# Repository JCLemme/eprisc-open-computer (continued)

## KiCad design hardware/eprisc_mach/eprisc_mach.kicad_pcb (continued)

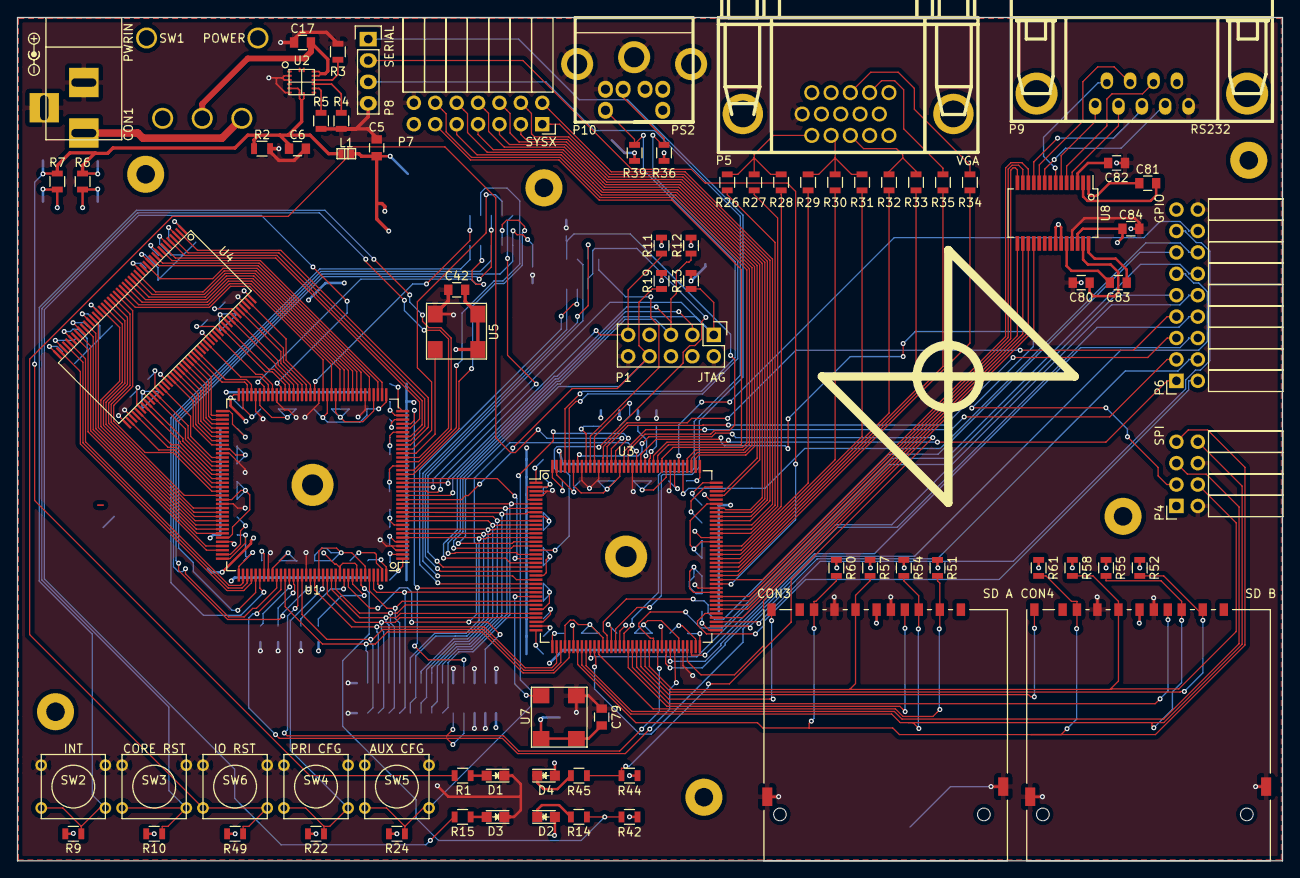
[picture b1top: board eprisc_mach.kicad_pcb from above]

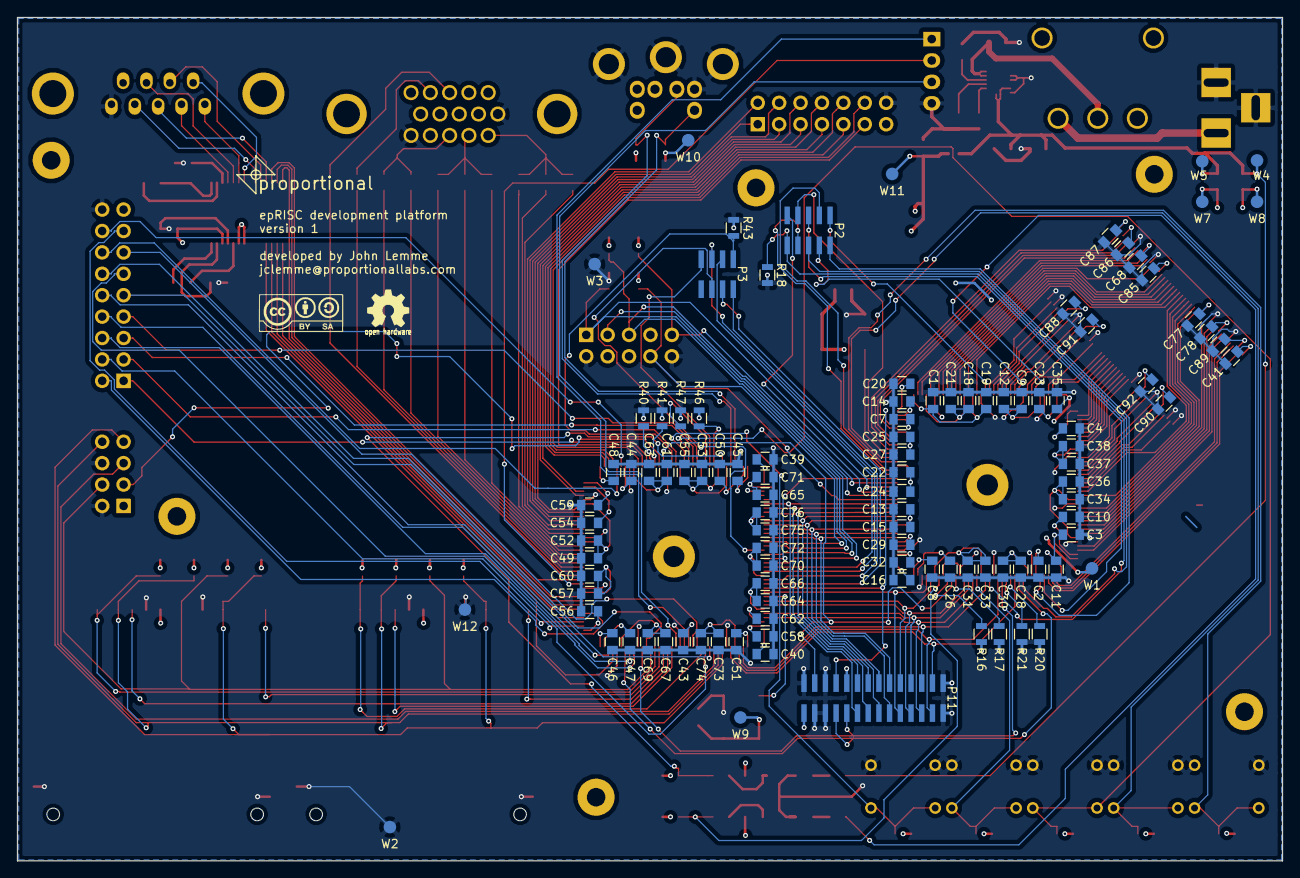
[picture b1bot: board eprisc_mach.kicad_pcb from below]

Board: 4 copper layers, 150.1 x 100.1 mm, 190 parts (107 on the bottom side), 210 nets.

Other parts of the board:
LOGO: logogood
LOGO_TINY: logotiny

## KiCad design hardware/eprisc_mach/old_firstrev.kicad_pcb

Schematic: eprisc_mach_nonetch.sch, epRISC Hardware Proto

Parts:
C1, C2, C3, C4, C7, C8, C9, C10, C11, C13, C14, C16, C18, C19, C20, C22, C23, C25, C26, C28, C29, C31, C32, C34, C35, C37, C40, C42, C43, C44, C45, C46, C47, C48, C49, C50, C51, C53, C54, C56, C57, C58, C59, C61, C62, C64, C65, C67, C68, C70, C71, C73, C75, C78, C79, C80, C81, C82, C83, C84: 0.1u; C_0805
C5: 10u; C_0805
C6: 47u/16v; C_0805
C12, C15, C21, C24, C27, C30, C33, C36, C38, C39, C41, C52, C55, C60, C63, C66, C69, C72, C74, C76, C77: 1u; C_0805
C17: 4.7u; C_0805
CON1: POWER_IN_5V; BARREL_JACK
CON2: SD_INT; microsd_socket
CON3: SD_A; SD_Card_Receptacle
CON4: SD_B; SD_Card_Receptacle
D1: GREEN; LED_0805
D2, D4: CONF_DONE; LED_0805
D3: HALT; LED_0805
L1: 600o/500mA; inductor_smd_4.8x2.8mm
L2, L3: FERRITE_BEAD; inductor_smd_0805
P1: PRI_PROG; Pin_Header_Straight_2x05
P2: PRI_DBG; Pin_Header_Straight_2x05
P3: AUX_DBG; Pin_Header_Straight_2x04
P4: AUX_PROG; Pin_Header_Straight_2x05
P5: VGA; DB_15F-VGA
P6: GPIO; Socket_Strip_Angled_2x09
P7: SYSX_EXT; Socket_Strip_Angled_2x07
P8: TTL_SERIAL; Socket_Strip_Straight_1x04
P9: RS232; DB_9F
P10: PS2; minidin-8
P11: SYSX_INT; bb080_28
R1, R13, R14, R15, R16, R17, R27, R30, R32, R38, R45, R46, R47: 1K; R_0805
R2: DNI; R_0805
R3, R4, R5, R8, R20, R21, R23, R40, R41: 0; R_0805
R6, R7: 0.1; R_0805
R9, R10, R42, R44: 3.3K; R_0805
R11, R12, R18, R19, R22, R24, R25, R36, R37, R39, R43, R48, R49: 10K; R_0805
R26, R29: 2K; R_0805
R28, R31, R33: 510; R_0805
R34, R35: 100; R_0805
R50, R51, R52, R53, R54, R55, R56, R57, R58, R59, R60, R61: 50K; R_0805
SW1: POWER; SW_SPDT
SW2: CORE_INT; smd_push2
SW3: CORE_RST; smd_push2
SW4: PRI_CONFIG; smd_push2
SW5: AUX_CONFIG; smd_push2
SW6: IO_RST; smd_push2
U1, U6: MAX10-10M16SA-E144; LQFP-144_20x20mm_Pitch0.5mm
U2: EP5388QI; QFN-16-ALTERA
U3: MCP1525; SOT-23
U4: IS45S32800J; TSOP-86
U5, U7: CB3LV-3C-50M0000; CRYSTAL_CTS
U8: MAX3244; SSOP-28_5.3x10.2mm_Pitch0.65mm
W1, W4, W5, W7, W8: TEST_1P; Measurement_Point_Round-SMD-Pad_Small
W2, W3, W6, W12: GND; Measurement_Point_Round-SMD-Pad_Small
W9: V_CORE; Measurement_Point_Round-SMD-Pad_Small
W10: V_IO; Measurement_Point_Round-SMD-Pad_Small
W11: V_VCCIO; Measurement_Point_Round-SMD-Pad_Small
W13: GNDA; Measurement_Point_Round-SMD-Pad_Small
W14: V_REF; Measurement_Point_Round-SMD-Pad_Small

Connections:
+2V5: C39.1, C41.1, C77.1, U1.5, U3.2, U6.5, W14.1
+3V3: C6.1, L1.1, R1.2, R2.1, R6.1, R7.1, U2.5 (VSENSE), U2.7 (VOUT), U2.8 (VOUT), W4.1, W5.1
+5V: C17.1, P10.4, SW1.2, U2.13 (ENABLE), U2.14 (VIN)
/AUX_CLK: U6.28, U7.3 (OUT)
/AUX_CONFDONE: R44.2, R45.2, U6.138
/AUX_CONFSEL: P3.1, R43.2, U6.126
/AUX_CRCERR: R47.2, U6.134
/AUX_DBG0: P3.3, U6.21
/AUX_DBG1: P3.5, U6.22
/AUX_DBG2: P3.2, U6.24
/AUX_DBG3: P3.4, U6.25
/AUX_DBG4: P3.6, U6.17
/AUX_DBG5: P3.7, U6.135
/AUX_DBG6: P3.8, U6.123
/AUX_DEVCLRN: R40.1, U6.121
/AUX_DEVOE: R41.1, U6.122
/AUX_JTAGEN: P4.8, R48.1, U6.15
/AUX_NCONFIG: R24.1, SW5.2, U6.129
/AUX_NSTATUS: R46.2, U6.136
/AUX_RST: R49.1, SW6.2, U6.130
/AUX_TCK: P4.1, R38.2, U6.18
/AUX_TDI: P4.9, R25.1, U6.19
/AUX_TDO: P4.3, U6.20
/AUX_TMS: P4.5, R37.1, U6.16
/BUS_CLK: P11.21, U1.33, U6.26
/BUS_INT: P11.25, U1.135, U6.124
/BUS_MISO0: P11.3, U1.141, U6.65
/BUS_MISO1: P11.15, U1.140, U6.69
/BUS_MISO2: P11.11, U1.130, U6.27
/BUS_MISO3: P11.13, U1.131, U6.29
/BUS_MISO4: P11.9, U1.132, U6.32
/BUS_MISO5: P11.7, U1.127, U6.33
/BUS_MISO6: P11.5, U1.124, U6.30
/BUS_MISO7: P11.17, U1.120, U6.64
/BUS_MOSI0: P11.4, U1.6, U6.6
/BUS_MOSI1: P11.6, U1.7, U6.7
/BUS_MOSI2: P11.8, U1.8, U6.8
/BUS_MOSI3: P11.10, U1.10, U6.10
/BUS_MOSI4: P11.12, U1.11, U6.11
/BUS_MOSI5: P11.14, U1.12, U6.12
/BUS_MOSI6: P11.16, U1.13, U6.13
/BUS_MOSI7: P11.18, U1.14, U6.14
/BUS_SS0: P11.20, U1.123, U6.62
/BUS_SS1: P11.22, U1.111, U6.66
/EXB_CLK: P7.12, U6.84
/EXB_INT: P7.11, U6.80
/EXB_MISO0: P7.1, U6.75
/EXB_MISO1: P7.3, U6.77
/EXB_MISO2: P7.5, U6.74
/EXB_MISO3: P7.7, U6.76
/EXB_MOSI0: P7.2, U6.79
/EXB_MOSI1: P7.4, U6.81
/EXB_MOSI2: P7.6, U6.85
/EXB_MOSI3: P7.8, U6.87
/EXB_SS0: P7.9, U6.86
/EXB_SS1: P7.10, U6.78
/GIO_PIN0: P6.1, U6.99
/GIO_PIN1: P6.3, U6.101
/GIO_PIN2: P6.5, U6.100
/GIO_PIN3: P6.7, U6.102
/GIO_PIN4: P6.9, U6.105
/GIO_PIN5: P6.11, U6.106
/GIO_PIN6: P6.13, U6.97
/GIO_PIN7: P6.15, U6.110
/GIO_PIN8: P6.2, U6.111
/GIO_PIN9: P6.4, U6.118
/GIO_PIN10: P6.6, U6.119
/GIO_PIN11: P6.8, U6.112
/GIO_PIN12: P6.10, U6.70
/GIO_PIN13: P6.12, U6.61
/GIO_PIN14: P6.14, U6.113
/GIO_PIN15: P6.16, U6.114
/MEM_A0: U1.61, U4.25 (A0)
/MEM_A1: U1.65, U4.26 (A1)
/MEM_A2: U1.64, U4.27 (A2)
/MEM_A3: U1.96, U4.60 (A3)
/MEM_A4: U1.93, U4.61 (A4)
/MEM_A5: U1.92, U4.62 (A5)
/MEM_A6: U1.91, U4.63 (A6)
/MEM_A7: U1.90, U4.64 (A7)
/MEM_A8: U1.89, U4.65 (A8)
/MEM_A9: U1.88, U4.66 (A9)
/MEM_A10: U1.44, U4.24 (A10)
/MEM_A11: U1.45, U4.21 (A11)
/MEM_BA0: U1.43, U4.22 (BA0)
/MEM_BA1: U1.41, U4.23 (BA1)
/MEM_CASn: U1.119, U4.18 (CASn)
/MEM_CKE: U1.110, U4.67 (CKE)
/MEM_CLK: U1.32, U4.68 (CLK)
/MEM_CSn: U1.114, U4.20 (CSn)
/MEM_DQ0: U1.55, U4.2 (DQ0)
/MEM_DQ1: U1.56, U4.4 (DQ1)
/MEM_DQ2: U1.57, U4.5 (DQ2)
/MEM_DQ3: U1.58, U4.7 (DQ3)
/MEM_DQ4: U1.46, U4.8 (DQ4)
/MEM_DQ5: U1.47, U4.10 (DQ5)
/MEM_DQ6: U1.50, U4.11 (DQ6)
/MEM_DQ7: U1.52, U4.13 (DQ7)
/MEM_DQ8: U1.60, U4.74 (DQ8)
/MEM_DQ9: U1.87, U4.76 (DQ9)
/MEM_DQ10: U1.86, U4.77 (DQ10)
/MEM_DQ11: U1.48, U4.79 (DQ11)
/MEM_DQ12: U1.85, U4.80 (DQ12)
/MEM_DQ13: U1.84, U4.82 (DQ13)
/MEM_DQ14: U1.81, U4.83 (DQ14)
/MEM_DQ15: U1.80, U4.85 (DQ15)
/MEM_DQ16: U1.69, U4.31 (DQ16)
/MEM_DQ17: U1.70, U4.33 (DQ17)
/MEM_DQ18: U1.74, U4.34 (DQ18)
/MEM_DQ19: U1.75, U4.36 (DQ19)
/MEM_DQ20: U1.76, U4.37 (DQ20)
/MEM_DQ21: U1.77, U4.39 (DQ21)
/MEM_DQ22: U1.78, U4.40 (DQ22)
/MEM_DQ23: U1.79, U4.42 (DQ23)
/MEM_DQ24: U1.106, U4.45 (DQ24)
/MEM_DQ25: U1.105, U4.47 (DQ25)
/MEM_DQ26: U1.102, U4.48 (DQ26)
/MEM_DQ27: U1.101, U4.50 (DQ27)
/MEM_DQ28: U1.100, U4.51 (DQ28)
/MEM_DQ29: U1.99, U4.53 (DQ29)
/MEM_DQ30: U1.98, U4.54 (DQ30)
/MEM_DQ31: U1.97, U4.56 (DQ31)
/MEM_DQM0: U1.21, U4.16 (DQM0)
/MEM_DQM1: U1.22, U4.71 (DQM1)
/MEM_DQM2: U1.24, U4.28 (DQM2)
/MEM_DQM3: U1.25, U4.59 (DQM3)
/MEM_RASn: U1.112, U4.19 (RASn)
/MEM_WEn: U1.118, U4.17 (WEn)
/PRI_CLK: U1.26, U5.3 (OUT)
/PRI_CONFDONE: R14.2, R42.2, U1.138
/PRI_CONFSEL: P2.1, R18.2, U1.126
/PRI_CRCERR: R17.2, U1.134
/PRI_DBG0: P2.2, U1.17
/PRI_DBG1: P2.4, U1.27
/PRI_DBG2: P2.6, U1.39
/PRI_DBG3: P2.8, U1.59
/PRI_DBG4: P2.10, U1.54
/PRI_DBG5: P2.9, U1.113
/PRI_DBGRX: P2.5, U1.38
/PRI_DBGTX: P2.7, U1.66
/PRI_DEVCLRN: R20.1, U1.121
/PRI_DEVOE: R21.1, U1.122
/PRI_FDBG: P2.3, U1.30
/PRI_FHLT: R15.2, U1.62
/PRI_INT: R9.1, SW2.2, U1.28
/PRI_JTAGEN: P1.8, R19.1, U1.15
/PRI_NCONFIG: R22.1, SW4.2, U1.129
/PRI_NSTATUS: R16.2, U1.136
/PRI_RST: R10.1, SW3.2, U1.29
/PRI_TCK: P1.1, R13.2, U1.18
/PRI_TDI: P1.9, R11.1, U1.19
/PRI_TDO: P1.3, U1.20
/PRI_TMS: P1.5, R12.1, U1.16
/PS2_CLK: P10.5, R39.2, U6.141
/PS2_DAT: P10.1, R36.2, U6.140
/SER_CTS: U6.45, U8.16 (R_OUT)
/SER_DCD: U6.48, U8.17 (R_OUT)
/SER_DSR: U6.43, U8.18 (R_OUT)
/SER_DTR: U6.41, U8.12 (T_IN)
/SER_RTS: U6.44, U8.13 (T_IN)
/SER_RX: U6.59, U8.15 (R_OUT)
/SER_TX: U6.60, U8.14 (T_IN)
/SPI_CD0: CON3.10 (CARD_DETECT), U6.131
/SPI_CD1: CON4.10 (CARD_DETECT), U6.132
/SPI_MISO: CON2.7, CON3.7 (DAT0), CON4.7 (DAT0), R59.2, R60.2, R61.2, U6.90
/SPI_MOSI: CON2.3, CON3.2 (CMD), CON4.2 (CMD), R53.2, R54.2, R55.2, U6.91
/SPI_SCLK: CON2.5, CON3.5 (CLK), CON4.5 (CLK), R56.2, R57.2, R58.2, U6.98
/SPI_SS0: CON2.2, R50.2, U6.92
/SPI_SS1: CON3.1 (CD/DAT3), R51.2, U6.93
/SPI_SS2: CON4.1 (CD/DAT3), R52.2, U6.96
/SPI_WP0: CON3.11 (WRITE_PROTECT), U6.120
/SPI_WP1: CON4.11 (WRITE_PROTECT), U6.127
/TTL_RTS: P8.3, U6.54
/TTL_RX: P8.1, U6.88
/TTL_TX: P8.2, U6.89
/VGA_B0: R32.2, U6.50
/VGA_B1: R33.2, U6.52
/VGA_G0: R29.2, U6.58
/VGA_G1: R30.2, U6.46
/VGA_G2: R31.2, U6.47
/VGA_HS: R34.2, U6.38
/VGA_R0: R26.2, U6.55
/VGA_R1: R27.2, U6.56
/VGA_R2: R28.2, U6.57
/VGA_VS: R35.2, U6.39
unnamed: C40.1, R8.1, U1.3
unnamed: C78.1, R23.1, U6.3
unnamed: C80.1, U8.27 (V+)
unnamed: C81.1, U8.1 (C2+)
unnamed: C81.2, U8.2 (C2-)
unnamed: C82.2, U8.3 (V-)
unnamed: C83.1, U8.28 (C1+)
unnamed: C83.2, U8.24 (C1-)
unnamed: CON1.1, SW1.1
unnamed: D1.2 (A), R1.1
unnamed: D2.2 (A), R14.1
unnamed: D3.2 (A), R15.1
unnamed: D4.2 (A), R45.1
unnamed: L2.1, U1.4
unnamed: L3.1, U6.4
unnamed: P5.1, R26.1, R27.1, R28.1
unnamed: P5.2, R29.1, R30.1, R31.1
unnamed: P5.3, R32.1, R33.1
unnamed: P5.13, R34.1
unnamed: P5.14, R35.1
unnamed: P9.1, U8.6 (R_IN)
unnamed: P9.2, U8.4 (R_IN)
unnamed: P9.3, U8.11 (T_OUT)
unnamed: P9.4, U8.9 (T_OUT)
unnamed: P9.6, U8.7 (R_IN)
unnamed: P9.7, U8.10 (T_OUT)
unnamed: P9.8, U8.5 (R_IN)
unnamed: R3.1, U2.12 (VS2)
unnamed: R4.1, U2.11 (VS1)
unnamed: R5.1, U2.10 (VS0)
VAA: C9.1, C12.1, C13.1, C15.1, C18.1, C21.1, C22.1, C24.1, C25.1, C27.1, C28.1, C30.1, C31.1, C33.1, C34.1, C36.1, C37.1, C38.1, C49.1, C52.1, C53.1, C55.1, C57.1, C60.1, C61.1, C63.1, C64.1, C66.1, C67.1, C69.1, C70.1, C72.1, C73.1, C74.1, C75.1, C76.1, C84.1, CON2.4, CON3.4 (VDD), CON4.4 (VDD), P1.4, P4.4, P6.17, P7.13, P11.28, R7.2, R9.2, R10.2, R11.2, R12.2, R16.1, R17.1, R19.2, R22.2, R24.2, R25.2, R36.1, R37.2, R39.1, R42.1, R44.1, R46.1, R47.1, R48.2, R49.2, R50.1, R51.1, R52.1, R53.1, R54.1, R55.1, R56.1, R57.1, R58.1, R59.1, R60.1, R61.1, U1.9, U1.23, U1.31, U1.40, U1.49, U1.67, U1.82, U1.94, U1.103, U1.117, U1.128, U1.139, U4.3 (VDDq), U4.9 (VDDq), U4.35 (VDDq), U4.41 (VDDq), U4.49 (VDDq), U4.55 (VDDq), U4.75 (VDDq), U4.81 (VDDq), U6.9, U6.23, U6.31, U6.40, U6.49, U6.67, U6.82, U6.94, U6.103, U6.117, U6.128, U6.139, U8.22 (FORCEOFFn), U8.23 (FORCEON), U8.26 (VCC), W8.1, W10.1
VCC: C1.1, C2.1, C3.1, C4.1, C7.1, C10.1, C14.1, C19.1, C23.1, C26.1, C29.1, C32.1, C42.2, C43.1, C44.1, C45.1, C46.1, C47.1, C50.1, C54.1, C58.1, C62.1, C65.1, C68.1, C71.1, C79.2, R6.2, U1.2, U1.34, U1.35, U1.71, U1.107, U1.143, U4.1 (VDD), U4.15 (VDD), U4.29 (VDD), U4.43 (VDD), U5.1 (EN), U5.4 (VCC), U6.2, U6.34, U6.35, U6.71, U6.107, U6.143, U7.1 (EN), U7.4 (VCC), W7.1, W9.1
VEE: C5.1, C8.1, C11.1, C16.1, C20.1, C35.1, C48.1, C51.1, C56.1, C59.1, L1.2, U1.1, U1.36, U1.37, U1.51, U1.72, U1.73, U1.108, U1.109, U1.115, U1.144, U3.1, U6.1, U6.36, U6.37, U6.51, U6.72, U6.73, U6.108, U6.109, U6.115, U6.144, W1.1, W11.1

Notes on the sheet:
What're these for?

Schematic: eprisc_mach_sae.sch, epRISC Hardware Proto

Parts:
C1, C2, C3, C4, C7, C8, C9, C10, C11, C13, C14, C16, C18, C19, C20, C22, C23, C25, C26, C28, C29, C31, C32, C34, C35, C37, C40, C42, C43, C44, C45, C46, C47, C48, C49, C50, C51, C53, C54, C56, C57, C58, C59, C61, C62, C64, C65, C67, C68, C70, C71, C73, C75, C78, C79, C80, C81, C82, C83, C84: 0.1u; C_0805
C5: 10u; C_0805
C6: 47u/16v; C_0805
C12, C15, C21, C24, C27, C30, C33, C36, C38, C39, C41, C52, C55, C60, C63, C66, C69, C72, C74, C76, C77: 1u; C_0805
C17: 4.7u; C_0805
CON1: POWER_IN_5V; BARREL_JACK
CON2: SD_INT; microsd_socket
CON3: SD_A; SD_Card_Receptacle
CON4: SD_B; SD_Card_Receptacle
D1: GREEN; LED_0805
D2, D4: CONF_DONE; LED_0805
D3: HALT; LED_0805
L1: 600o/500mA; inductor_smd_0603
L2, L3: FERRITE_BEAD; inductor_smd_0402
P1: PRI_PROG; SMD_STRIP_10
P2: PRI_DBG; SMD_STRIP_10
P3: AUX_DBG; SMD_STRIP_8
P4: AUX_PROG; SMD_STRIP_10
P5: VGA; DB15F-VGA-AMP
P6: GPIO; Socket_Strip_Angled_2x09
P7: SYSX_EXT; Socket_Strip_Angled_2x07
P8: TTL_SERIAL; Socket_Strip_Straight_1x04
P9: RS232; DB_9F
P10: PS2; 00JG-MiniDin6
P11: SYSX_INT; SMD_STRIP_28
R1, R13, R14, R15, R16, R17, R27, R30, R32, R38, R45, R46, R47: 1K; R_0805
R2: DNI; R_0805
R3, R4, R5, R8, R20, R21, R23, R40, R41: 0; R_0805
R6, R7: 0.1; R_0805
R9, R10, R42, R44: 3.3K; R_0805
R11, R12, R18, R19, R22, R24, R25, R36, R37, R39, R43, R48, R49, R50, R51, R52, R53, R54, R55, R56, R57, R58, R59, R60, R61: 10K; R_0805
R26, R29: 2K; R_0805
R28, R31, R33: 510; R_0805
R34, R35: 100; R_0805
SW1: POWER; SW_SLIDE_PWR
SW2: CORE_INT; smd_push2
SW3: CORE_RST; smd_push2
SW4: PRI_CONFIG; smd_push2
SW5: AUX_CONFIG; smd_push2
SW6: IO_RST; smd_push2
U1, U6: MAX10-10M16SA-E144; LQFP-144_20x20mm_Pitch0.5mm
U2: EP5388QI; QFN-16-ALTERA
U3: MCP1525; SOT-23
U4: IS45S32800J; TSOP-86
U5, U7: CB3LV-3C-50M0000; CRYSTAL_CTS
U8: MAX3244; SSOP-28_5.3x10.2mm_Pitch0.65mm
W1, W4, W5, W7, W8: TEST_1P; Measurement_Point_Round-SMD-Pad_Small
W2, W3, W6, W12: GND; Measurement_Point_Round-SMD-Pad_Small
W9: V_CORE; Measurement_Point_Round-SMD-Pad_Small
W10: V_IO; Measurement_Point_Round-SMD-Pad_Small
W11: V_VCCIO; Measurement_Point_Round-SMD-Pad_Small
W13: GNDA; Measurement_Point_Round-SMD-Pad_Small
W14: V_REF; Measurement_Point_Round-SMD-Pad_Small

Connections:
+2V5: C39.1, C41.1, C77.1, U1.5, U3.2, U6.5, W14.1
+3V3: C6.1, L1.1, R1.2, R2.1, R6.1, R7.1, U2.5 (VSENSE), U2.7 (VOUT), U2.8 (VOUT), W4.1, W5.1
+5V: C17.1, P10.4, SW1.2, U2.13 (ENABLE), U2.14 (VIN)
/AUX_CLK: U6.28, U7.3 (OUT)
/AUX_CONFDONE: R44.2, R45.2, U6.138
/AUX_CONFSEL: P3.1, R43.2, U6.126
/AUX_CRCERR: R47.2, U6.134
/AUX_DBG0: P3.3, U6.21
/AUX_DBG1: P3.5, U6.22
/AUX_DBG2: P3.2, U6.24
/AUX_DBG3: P3.4, U6.25
/AUX_DBG4: P3.6, U6.17
/AUX_DBG5: P3.7, U6.135
/AUX_DBG6: P3.8, U6.123
/AUX_DEVCLRN: R40.1, U6.121
/AUX_DEVOE: R41.1, U6.122
/AUX_JTAGEN: P4.8, R48.1, U6.15
/AUX_NCONFIG: R24.1, SW5.2, U6.129
/AUX_NSTATUS: R46.2, U6.136
/AUX_RST: R49.1, SW6.2, U6.130
/AUX_TCK: P4.1, R38.2, U6.18
/AUX_TDI: P4.9, R25.1, U6.19
/AUX_TDO: P4.3, U6.20
/AUX_TMS: P4.5, R37.1, U6.16
/BUS_CLK: P11.21, U1.33, U6.26
/BUS_INT: P11.25, U1.135, U6.124
/BUS_MISO0: P11.3, U1.141, U6.65
/BUS_MISO1: P11.15, U1.140, U6.69
/BUS_MISO2: P11.11, U1.130, U6.27
/BUS_MISO3: P11.13, U1.131, U6.29
/BUS_MISO4: P11.9, U1.132, U6.32
/BUS_MISO5: P11.7, U1.127, U6.33
/BUS_MISO6: P11.5, U1.124, U6.30
/BUS_MISO7: P11.17, U1.120, U6.64
/BUS_MOSI0: P11.4, U1.6, U6.6
/BUS_MOSI1: P11.6, U1.7, U6.7
/BUS_MOSI2: P11.8, U1.8, U6.8
/BUS_MOSI3: P11.10, U1.10, U6.10
/BUS_MOSI4: P11.12, U1.11, U6.11
/BUS_MOSI5: P11.14, U1.12, U6.12
/BUS_MOSI6: P11.16, U1.13, U6.13
/BUS_MOSI7: P11.18, U1.14, U6.14
/BUS_SS0: P11.20, U1.123, U6.62
/BUS_SS1: P11.22, U1.111, U6.66
/EXB_CLK: P7.12, U6.84
/EXB_INT: P7.11, U6.80
/EXB_MISO0: P7.1, U6.75
/EXB_MISO1: P7.3, U6.77
/EXB_MISO2: P7.5, U6.74
/EXB_MISO3: P7.7, U6.76
/EXB_MOSI0: P7.2, U6.79
/EXB_MOSI1: P7.4, U6.81
/EXB_MOSI2: P7.6, U6.85
/EXB_MOSI3: P7.8, U6.87
/EXB_SS0: P7.9, U6.86
/EXB_SS1: P7.10, U6.78
/GIO_PIN0: P6.1, U6.99
/GIO_PIN1: P6.3, U6.101
/GIO_PIN2: P6.5, U6.100
/GIO_PIN3: P6.7, U6.102
/GIO_PIN4: P6.9, U6.105
/GIO_PIN5: P6.11, U6.106
/GIO_PIN6: P6.13, U6.97
/GIO_PIN7: P6.15, U6.110
/GIO_PIN8: P6.2, U6.111
/GIO_PIN9: P6.4, U6.118
/GIO_PIN10: P6.6, U6.119
/GIO_PIN11: P6.8, U6.112
/GIO_PIN12: P6.10, U6.70
/GIO_PIN13: P6.12, U6.61
/GIO_PIN14: P6.14, U6.113
/GIO_PIN15: P6.16, U6.114
/MEM_A0: U1.61, U4.25 (A0)
/MEM_A1: U1.65, U4.26 (A1)
/MEM_A2: U1.64, U4.27 (A2)
/MEM_A3: U1.96, U4.60 (A3)
/MEM_A4: U1.93, U4.61 (A4)
/MEM_A5: U1.92, U4.62 (A5)
/MEM_A6: U1.91, U4.63 (A6)
/MEM_A7: U1.90, U4.64 (A7)
/MEM_A8: U1.89, U4.65 (A8)
/MEM_A9: U1.88, U4.66 (A9)
/MEM_A10: U1.44, U4.24 (A10)
/MEM_A11: U1.45, U4.21 (A11)
/MEM_BA0: U1.43, U4.22 (BA0)
/MEM_BA1: U1.41, U4.23 (BA1)
/MEM_CASn: U1.119, U4.18 (CASn)
/MEM_CKE: U1.110, U4.67 (CKE)
/MEM_CLK: U1.32, U4.68 (CLK)
/MEM_CSn: U1.114, U4.20 (CSn)
/MEM_DQ0: U1.55, U4.2 (DQ0)
/MEM_DQ1: U1.56, U4.4 (DQ1)
/MEM_DQ2: U1.57, U4.5 (DQ2)
/MEM_DQ3: U1.58, U4.7 (DQ3)
/MEM_DQ4: U1.46, U4.8 (DQ4)
/MEM_DQ5: U1.47, U4.10 (DQ5)
/MEM_DQ6: U1.50, U4.11 (DQ6)
/MEM_DQ7: U1.52, U4.13 (DQ7)
/MEM_DQ8: U1.60, U4.74 (DQ8)
/MEM_DQ9: U1.87, U4.76 (DQ9)
/MEM_DQ10: U1.86, U4.77 (DQ10)
/MEM_DQ11: U1.48, U4.79 (DQ11)
/MEM_DQ12: U1.85, U4.80 (DQ12)
/MEM_DQ13: U1.84, U4.82 (DQ13)
/MEM_DQ14: U1.81, U4.83 (DQ14)
/MEM_DQ15: U1.80, U4.85 (DQ15)
/MEM_DQ16: U1.69, U4.31 (DQ16)
/MEM_DQ17: U1.70, U4.33 (DQ17)
/MEM_DQ18: U1.74, U4.34 (DQ18)
/MEM_DQ19: U1.75, U4.36 (DQ19)
/MEM_DQ20: U1.76, U4.37 (DQ20)
/MEM_DQ21: U1.77, U4.39 (DQ21)
/MEM_DQ22: U1.78, U4.40 (DQ22)
/MEM_DQ23: U1.79, U4.42 (DQ23)
/MEM_DQ24: U1.106, U4.45 (DQ24)
/MEM_DQ25: U1.105, U4.47 (DQ25)
/MEM_DQ26: U1.102, U4.48 (DQ26)
/MEM_DQ27: U1.101, U4.50 (DQ27)
/MEM_DQ28: U1.100, U4.51 (DQ28)
/MEM_DQ29: U1.99, U4.53 (DQ29)
/MEM_DQ30: U1.98, U4.54 (DQ30)
/MEM_DQ31: U1.97, U4.56 (DQ31)
/MEM_DQM0: U1.21, U4.16 (DQM0)
/MEM_DQM1: U1.22, U4.71 (DQM1)
/MEM_DQM2: U1.24, U4.28 (DQM2)
/MEM_DQM3: U1.25, U4.59 (DQM3)
/MEM_RASn: U1.112, U4.19 (RASn)
/MEM_WEn: U1.118, U4.17 (WEn)
/PRI_CLK: U1.26, U5.3 (OUT)
/PRI_CONFDONE: R14.2, R42.2, U1.138
/PRI_CONFSEL: P2.1, R18.2, U1.126
/PRI_CRCERR: R17.2, U1.134
/PRI_DBG0: P2.2, U1.17
/PRI_DBG1: P2.4, U1.27
/PRI_DBG2: P2.6, U1.39
/PRI_DBG3: P2.8, U1.59
/PRI_DBG4: P2.10, U1.54
/PRI_DBG5: P2.9, U1.113
/PRI_DBGRX: P2.5, U1.38
/PRI_DBGTX: P2.7, U1.66
/PRI_DEVCLRN: R20.1, U1.121
/PRI_DEVOE: R21.1, U1.122
/PRI_FDBG: P2.3, U1.30
/PRI_FHLT: R15.2, U1.62
/PRI_INT: R9.1, SW2.2, U1.28
/PRI_JTAGEN: P1.8, R19.1, U1.15
/PRI_NCONFIG: R22.1, SW4.2, U1.129
/PRI_NSTATUS: R16.2, U1.136
/PRI_RST: R10.1, SW3.2, U1.29
/PRI_TCK: P1.1, R13.2, U1.18
/PRI_TDI: P1.9, R11.1, U1.19
/PRI_TDO: P1.3, U1.20
/PRI_TMS: P1.5, R12.1, U1.16
/PS2_CLK: P10.5, R39.2, U6.141
/PS2_DAT: P10.1, R36.2, U6.140
/SER_CTS: U6.45, U8.16 (R_OUT)
/SER_DCD: U6.48, U8.17 (R_OUT)
/SER_DSR: U6.43, U8.18 (R_OUT)
/SER_DTR: U6.41, U8.12 (T_IN)
/SER_RTS: U6.44, U8.13 (T_IN)
/SER_RX: U6.59, U8.15 (R_OUT)
/SER_TX: U6.60, U8.14 (T_IN)
/SPI_CD0: CON3.10 (CARD_DETECT), U6.131
/SPI_CD1: CON4.10 (CARD_DETECT), U6.132
/SPI_MISO: CON2.7, CON3.7 (DAT0), CON4.7 (DAT0), R59.2, R60.2, R61.2, U6.90
/SPI_MOSI: CON2.3, CON3.2 (CMD), CON4.2 (CMD), R53.2, R54.2, R55.2, U6.91
/SPI_SCLK: CON2.5, CON3.5 (CLK), CON4.5 (CLK), R56.2, R57.2, R58.2, U6.98
/SPI_SS0: CON2.2, R50.2, U6.92
/SPI_SS1: CON3.1 (CD/DAT3), R51.2, U6.93
/SPI_SS2: CON4.1 (CD/DAT3), R52.2, U6.96
/SPI_WP0: CON3.11 (WRITE_PROTECT), U6.120
/SPI_WP1: CON4.11 (WRITE_PROTECT), U6.127
/TTL_RTS: P8.3, U6.54
/TTL_RX: P8.1, U6.88
/TTL_TX: P8.2, U6.89
/VGA_B0: R32.2, U6.50
/VGA_B1: R33.2, U6.52
/VGA_G0: R29.2, U6.58
/VGA_G1: R30.2, U6.46
/VGA_G2: R31.2, U6.47
/VGA_HS: R34.2, U6.38
/VGA_R0: R26.2, U6.55
/VGA_R1: R27.2, U6.56
/VGA_R2: R28.2, U6.57
/VGA_VS: R35.2, U6.39
unnamed: C40.1, R8.1, U1.3
unnamed: C78.1, R23.1, U6.3
unnamed: C80.1, U8.27 (V+)
unnamed: C81.1, U8.1 (C2+)
unnamed: C81.2, U8.2 (C2-)
unnamed: C82.2, U8.3 (V-)
unnamed: C83.1, U8.28 (C1+)
unnamed: C83.2, U8.24 (C1-)
unnamed: CON1.1, SW1.1
unnamed: D1.2 (A), R1.1
unnamed: D2.2 (A), R14.1
unnamed: D3.2 (A), R15.1
unnamed: D4.2 (A), R45.1
unnamed: L2.1, U1.4
unnamed: L3.1, U6.4
unnamed: P5.1, R26.1, R27.1, R28.1
unnamed: P5.2, R29.1, R30.1, R31.1
unnamed: P5.3, R32.1, R33.1
unnamed: P5.13, R34.1
unnamed: P5.14, R35.1
unnamed: P9.1, U8.6 (R_IN)
unnamed: P9.2, U8.4 (R_IN)
unnamed: P9.3, U8.11 (T_OUT)
unnamed: P9.4, U8.9 (T_OUT)
unnamed: P9.6, U8.7 (R_IN)
unnamed: P9.7, U8.10 (T_OUT)
unnamed: P9.8, U8.5 (R_IN)
unnamed: R3.1, U2.12 (VS2)
unnamed: R4.1, U2.11 (VS1)
unnamed: R5.1, U2.10 (VS0)
VAA: C9.1, C12.1, C13.1, C15.1, C18.1, C21.1, C22.1, C24.1, C25.1, C27.1, C28.1, C30.1, C31.1, C33.1, C34.1, C36.1, C37.1, C38.1, C49.1, C52.1, C53.1, C55.1, C57.1, C60.1, C61.1, C63.1, C64.1, C66.1, C67.1, C69.1, C70.1, C72.1, C73.1, C74.1, C75.1, C76.1, C84.1, CON2.4, CON3.4 (VDD), CON4.4 (VDD), P1.4, P4.4, P6.17, P7.13, P11.28, R7.2, R9.2, R10.2, R11.2, R12.2, R16.1, R17.1, R19.2, R22.2, R24.2, R25.2, R36.1, R37.2, R39.1, R42.1, R44.1, R46.1, R47.1, R48.2, R49.2, R50.1, R51.1, R52.1, R53.1, R54.1, R55.1, R56.1, R57.1, R58.1, R59.1, R60.1, R61.1, U1.9, U1.23, U1.31, U1.40, U1.49, U1.67, U1.82, U1.94, U1.103, U1.117, U1.128, U1.139, U4.3 (VDDq), U4.9 (VDDq), U4.35 (VDDq), U4.41 (VDDq), U4.49 (VDDq), U4.55 (VDDq), U4.75 (VDDq), U4.81 (VDDq), U6.9, U6.23, U6.31, U6.40, U6.49, U6.67, U6.82, U6.94, U6.103, U6.117, U6.128, U6.139, U8.22 (FORCEOFFn), U8.23 (FORCEON), U8.26 (VCC), W8.1, W10.1
VCC: C1.1, C2.1, C3.1, C4.1, C7.1, C10.1, C14.1, C19.1, C23.1, C26.1, C29.1, C32.1, C42.2, C43.1, C44.1, C45.1, C46.1, C47.1, C50.1, C54.1, C58.1, C62.1, C65.1, C68.1, C71.1, C79.2, R6.2, U1.2, U1.34, U1.35, U1.71, U1.107, U1.143, U4.1 (VDD), U4.15 (VDD), U4.29 (VDD), U4.43 (VDD), U5.1 (EN), U5.4 (VCC), U6.2, U6.34, U6.35, U6.71, U6.107, U6.143, U7.1 (EN), U7.4 (VCC), W7.1, W9.1
VEE: C5.1, C8.1, C11.1, C16.1, C20.1, C35.1, C48.1, C51.1, C56.1, C59.1, L1.2, U1.1, U1.36, U1.37, U1.51, U1.72, U1.73, U1.108, U1.109, U1.115, U1.144, U3.1, U6.1, U6.36, U6.37, U6.51, U6.72, U6.73, U6.108, U6.109, U6.115, U6.144, W1.1, W11.1

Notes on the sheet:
What're these for?

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
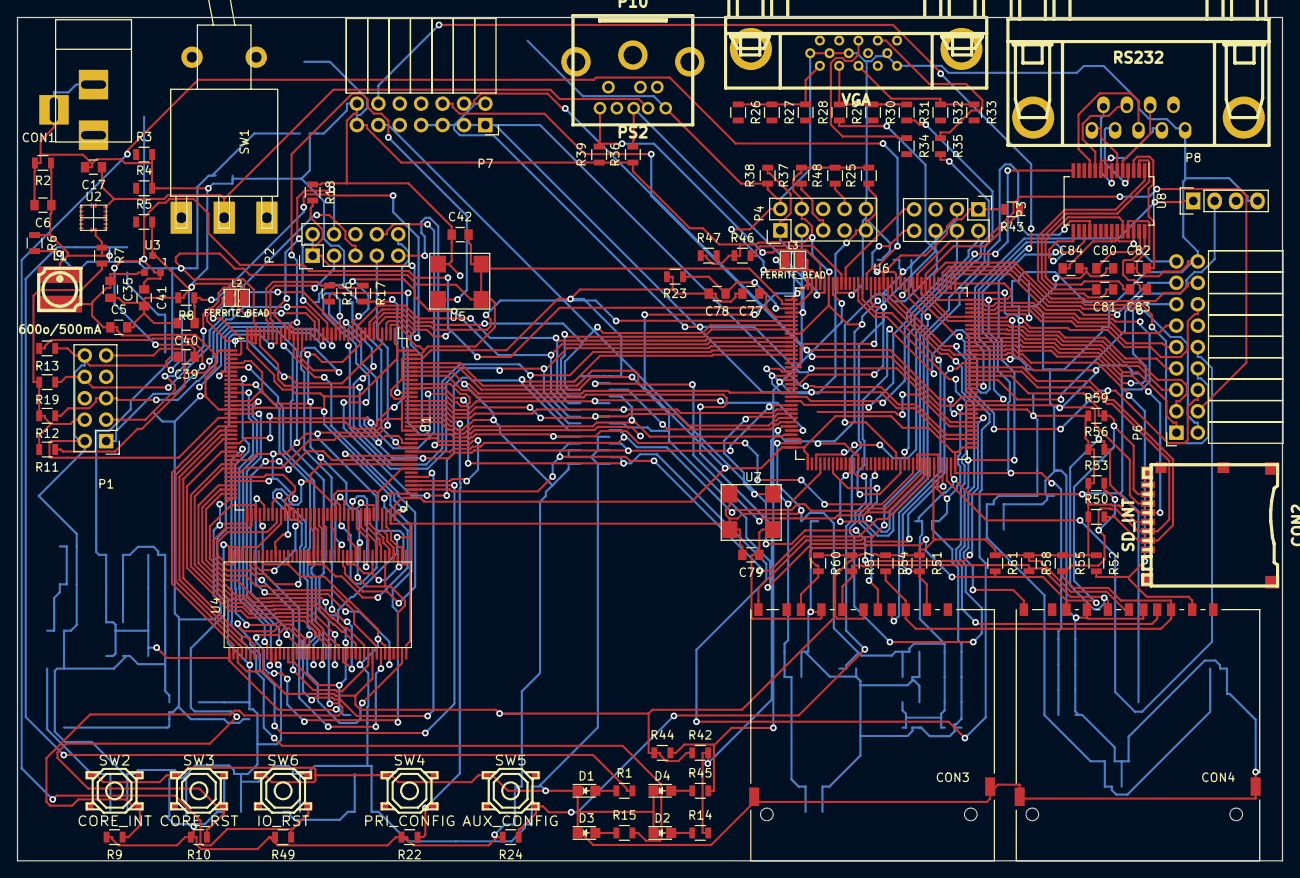
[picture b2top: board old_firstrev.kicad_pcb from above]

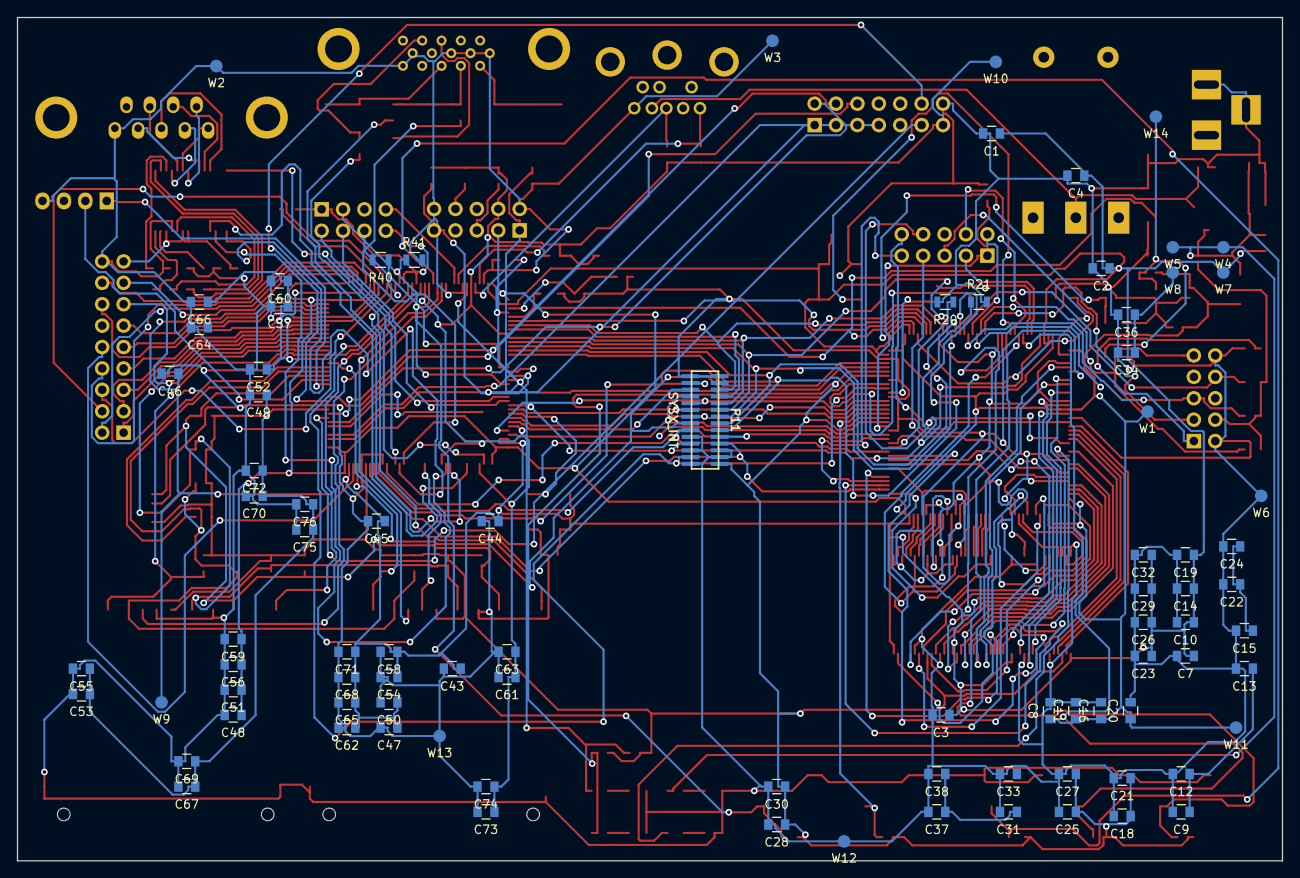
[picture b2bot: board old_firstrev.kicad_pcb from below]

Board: 4 copper layers, 150.1 x 100.1 mm, 195 parts (87 on the bottom side), 219 nets.

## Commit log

2016-10-19 Initial file upload
2016-10-21 License updates
2016-10-23 Added licenses
2016-10-23 Working on new ISA
2016-10-25 ISA v5 is looking good
2016-10-27 Interrupt behavior better defined
2016-10-27 Undefined is a nice word
2016-11-01 Progress
2016-11-14 Interrupts will be finished later - using a simpler version for now
2016-11-18 Filename changes, plus template for new core
2016-11-23 Definitions for v5 implementation plus doc cleanup
2016-12-13 Still at it
2016-12-19 More changes
2017-01-05 Almost finished with core
2017-01-09 Added testbench for core
2017-01-09 Core implementation: branching, no-op OK
2017-01-10 Fixed register swap issue
2017-01-10 Created testbench makefile, moved directories
2017-01-10 Tidying core directory for machine
2017-01-10 Fixed makefile
2017-01-11 Fixed issue with pop load instruction
2017-01-11 Actually fixed it this time
2017-01-11 Interrupts are a go
2017-01-11 Removing single-step on processor (for now at least)
2017-01-17 Documentation cleanup, assembly/sysX spec, added spasm to repo
2017-01-17 Added build instructions to the README
2017-01-18 Added to-do list
2017-01-20 Roadmap update
2017-01-30 Starting machine
2017-01-30 Something, but I forget what
2017-02-01 Machine:
2017-02-01 Added that one file
2017-02-01 Transfer
2017-02-07 More controller
2017-02-08 Tweak in sysx
2017-02-08 Bus controller done?
2017-02-09 Bus controller done 2?
2017-02-10 Bus controller done/not debugged, some core bugs
2017-02-13 I/O controller coming along nicely
2017-02-13 Added old system's I/O modules, for reference purposes
2017-03-01 Core modifications for synthesis
2017-03-06 Added Quartus project for primary FPGA
2017-03-07 Fix project
2017-03-11 Transfer commit
2017-03-11 Controller patches for synthesis
2017-03-13 Bugfixes and I/O controller setup
2017-03-16 Hopefully all working now
2017-03-18 UART is also working now
2017-03-18 v5 assembly def. is done, spasm ported
2017-04-03 Fixed the messed up tree
2017-04-03 Git is fixed now
2017-04-05 Readme update
2017-04-25 Computer breaking, backing up now
2017-05-07 Machine changes
2017-05-08 Lemon
2017-05-10 Lemon done?
2017-05-11 Lemon broke
2017-05-12 Lemon more done
2017-05-12 Lemon block requests are OK
2017-05-16 Lemon OK
2017-05-18 SD cards?
2017-05-26 SD card initializes
2017-05-29 Close
2017-05-29 Video bug
2017-05-30 aaaa
2017-05-30 Software
2017-06-01 Video fix?
2017-06-01 Video working now
2017-06-04 Kinda done
2017-06-05 Good
2017-07-25 Weeeeee
2017-09-13 Transfer to lappy
2018-05-12 flail work and ext2 support beginnings
2018-05-12 spasm work
